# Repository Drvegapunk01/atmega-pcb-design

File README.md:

This PCB was designed using Eagle software

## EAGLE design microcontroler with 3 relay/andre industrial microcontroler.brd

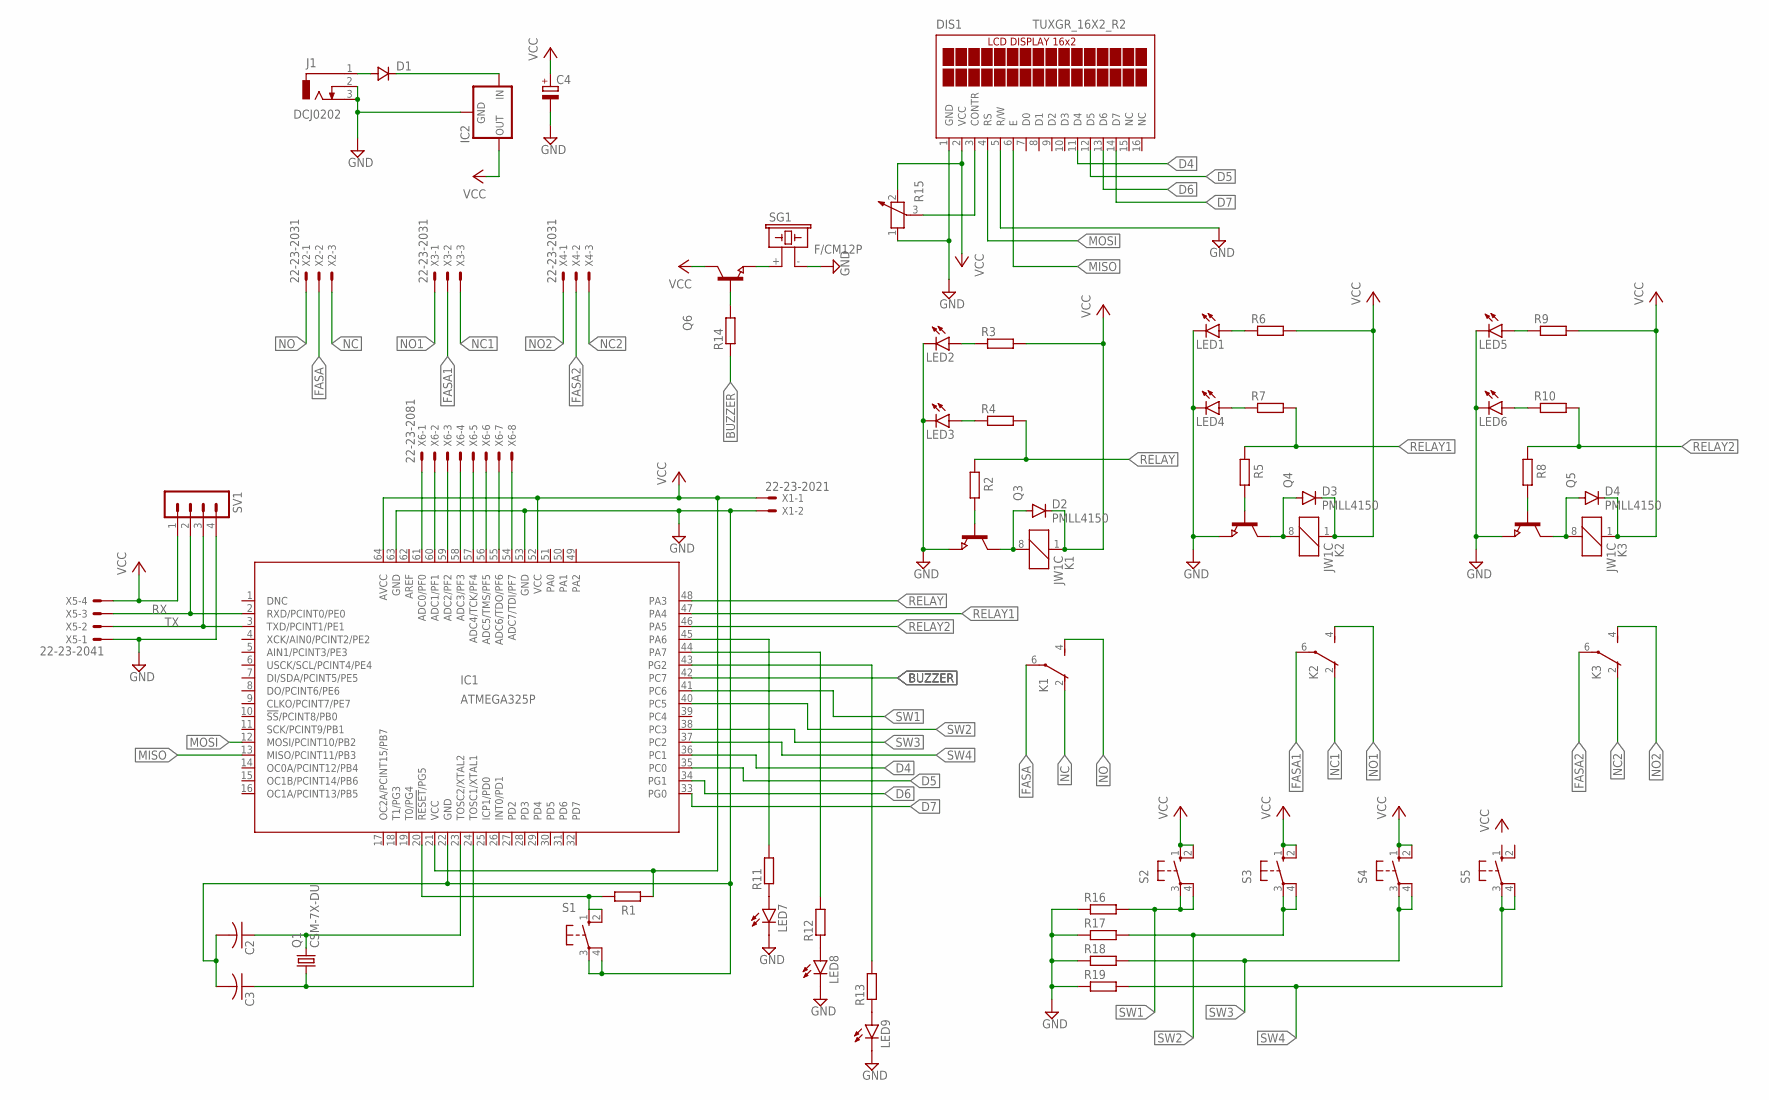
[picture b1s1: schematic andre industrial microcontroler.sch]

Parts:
C2, C3: C-US025-024X044; C025-024X044
C4: CPOL-EU140CLH-0810; 140CLH-0810
D1: DSOD323; SOD323
D2, D3, D4: PMLL4150; SOD80C
DIS1: TUXGR_16X2_R2
IC1: ATMEGA325P; 64M1
IC2: 78XXS
J1: DCJ0202
K1, K2, K3: JW1C
LED1, LED2, LED3, LED4, LED5, LED6, LED7, LED8, LED9: LEDCHIP-LED0805; CHIP-LED0805
Q1: CSM-7X-DU
Q3, Q4, Q5, Q6: NPN-TRANSISTOR_SOT23; SOT23
R1, R2, R3, R4, R5, R6, R7, R8, R9, R10, R11, R12, R13, R14, R16, R17, R18, R19: R-EU_R0805; R0805
R15: POTENTIOMETER_PT-10; PT-10
S1, S2, S3, S4, S5: 10-XX; B3F-10XX
SG1: F/CM12P
SV1: MA04-1
X1: 22-23-2021
X2, X3, X4: 22-23-2031
X5: 22-23-2041
X6: 22-23-2081

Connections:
BUZZER: IC1.42 (PC7), R14.1
D4: DIS1.11 (D4), IC1.36 (PC1)
D5: DIS1.12 (D5), IC1.35 (PC0)
D6: DIS1.13 (D6), IC1.34 (PG1)
D7: DIS1.14 (D7), IC1.33 (PG0)
FASA: K1.6, X2.2
FASA1: K2.6, X3.2
FASA2: K3.6, X4.2
GND: C2.2, C3.2, C4.-, DIS1.1 (GND), DIS1.5 (R/W), IC1.22 (GND), IC1.53 (GND), IC1.63 (GND), IC2.GND, J1.2, J1.3, LED1.C, LED2.C, LED3.C, LED4.C, LED5.C, LED6.C, LED7.C, LED8.C, LED9.C, Q3.2 (E), Q4.2 (E), Q5.2 (E), R15.1, R16.1, R17.1, R18.1, R19.1, S1.3, S1.4 (P1), SG1.- (2), SV1.4, X1.2, X5.1
MISO: DIS1.6 (E), IC1.13 (MISO/PCINT11/PB3)
MOSI: DIS1.4 (RS), IC1.12 (MOSI/PCINT10/PB2)
unnamed: IC1.20 (!RESET!/PG5), R1.1, S1.1 (S), S1.2 (S1)
unnamed: D1.1 (C), IC2.IN
unnamed: D1.2 (A), J1.1
unnamed: C2.1, IC1.23 (TOSC2/XTAL2), Q1.2
unnamed: C3.1, IC1.24 (TOSC1/XTAL1), Q1.1
unnamed: D3.A, K2.8 (2), Q4.3 (C)
unnamed: D2.A, K1.8 (2), Q3.3 (C)
unnamed: Q4.1 (B), R5.1
unnamed: Q3.1 (B), R2.1
unnamed: LED3.A, R4.1
unnamed: LED2.A, R3.1
unnamed: LED4.A, R7.1
unnamed: LED1.A, R6.1
unnamed: D4.A, K3.8 (2), Q5.3 (C)
unnamed: Q5.1 (B), R8.1
unnamed: LED6.A, R10.1
unnamed: LED5.A, R9.1
unnamed: LED9.A, R13.1
unnamed: IC1.43 (PG2), R13.2
unnamed: IC1.45 (PA6), R11.2
unnamed: LED7.A, R11.1
unnamed: IC1.44 (PA7), R12.2
unnamed: LED8.A, R12.1
unnamed: IC1.61 (ADC0/PF0), X6.1
unnamed: IC1.60 (ADC1/PF1), X6.2
unnamed: IC1.59 (ADC2/PF2), X6.3
unnamed: IC1.58 (ADC3/PF3), X6.4
unnamed: IC1.57 (ADC4/TCK/PF4), X6.5
unnamed: IC1.56 (ADC5/TMS/PF5), X6.6
unnamed: IC1.55 (ADC6/TDO/PF6), X6.7
unnamed: IC1.54 (ADC7/TDI/PF7), X6.8
unnamed: Q6.2 (E), SG1.+ (1)
unnamed: Q6.1 (B), R14.2
unnamed: DIS1.3 (CONTR), R15.3
NC: K1.2 (O), X2.3
NC1: K2.2 (O), X3.3
NC2: K3.2 (O), X4.3
NO: K1.4 (S), X2.1
NO1: K2.4 (S), X3.1
NO2: K3.4 (S), X4.1
RELAY: IC1.48 (PA3), R2.2, R4.2
RELAY1: IC1.47 (PA4), R5.2, R7.2
RELAY2: IC1.46 (PA5), R8.2, R10.2
RX: IC1.2 (RXD/PCINT0/PE0), SV1.2, X5.3
SW1: IC1.41 (PC6), R16.2, S2.3, S2.4 (P1)
SW2: IC1.40 (PC5), R17.2, S3.3, S3.4 (P1)
SW3: IC1.38 (PC3), R18.2, S4.3, S4.4 (P1)
SW4: IC1.37 (PC2), R19.2, S5.3, S5.4 (P1)
TX: IC1.3 (TXD/PCINT1/PE1), SV1.3, X5.2
VCC: C4.+, D2.C, D3.C, D4.C, DIS1.2 (VCC), IC1.21 (VCC), IC1.52 (VCC), IC1.64 (AVCC), IC2.OUT, K1.1, K2.1, K3.1, Q6.3 (C), R1.2, R3.2, R6.2, R9.2, R15.2, S2.1 (S), S2.2 (S1), S3.1 (S), S3.2 (S1), S4.1 (S), S4.2 (S1), SV1.1, X1.1, X5.4

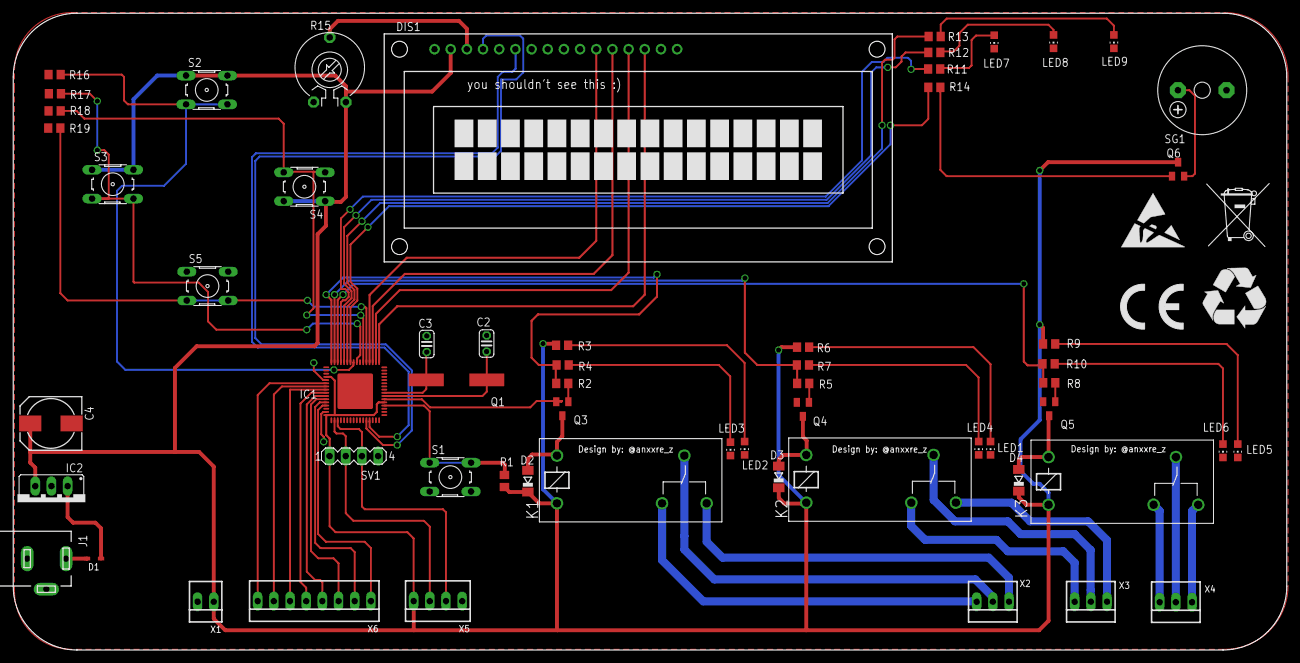
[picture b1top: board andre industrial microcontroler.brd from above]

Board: 2 copper layers, 200.0 x 100.0 mm, 64 parts (0 on the bottom side), 61 nets.

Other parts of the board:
U$1: MUELLTONNE_10.00
U$2: ESD_10.00
U$3: RECYCLING_10.00
U$4: CE_7.3MM

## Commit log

2024-11-28 README.md
